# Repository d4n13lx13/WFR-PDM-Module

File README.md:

# WFR-PDM-Module
WFR GLV 2021 PDM PCB
8 fuseholders with diagnosis LEDs, Undervoltage Protection Circuit.

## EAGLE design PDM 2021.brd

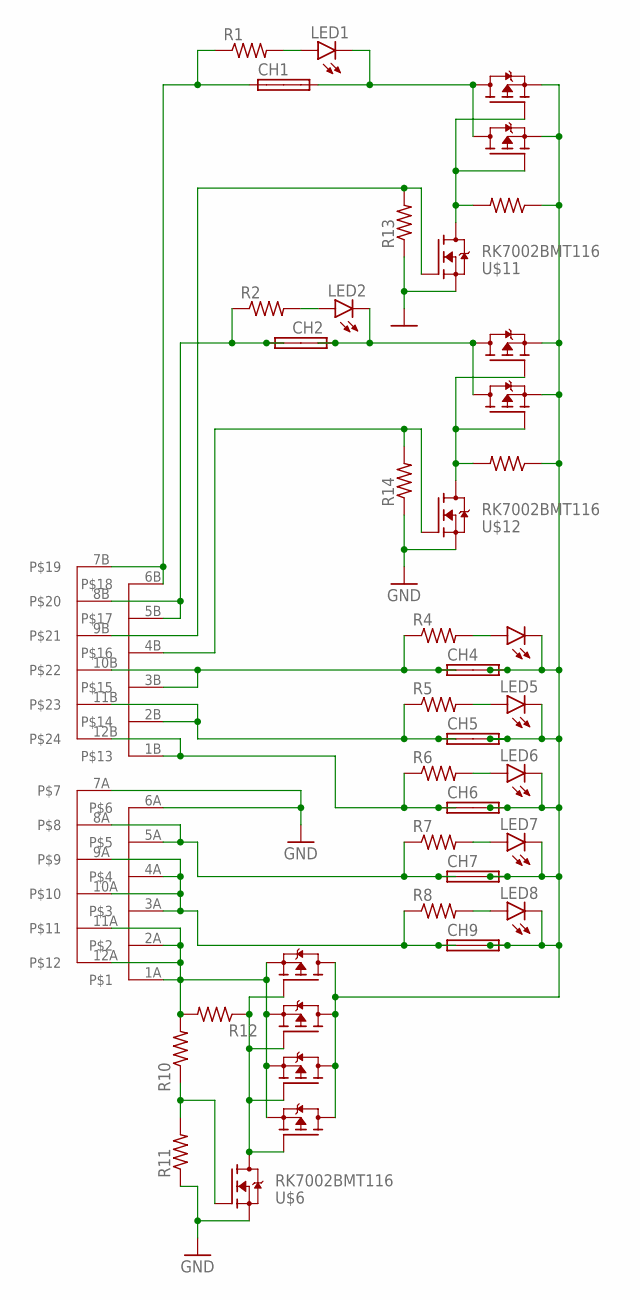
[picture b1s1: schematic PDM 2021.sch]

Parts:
CH1, CH2, CH4, CH5, CH6, CH7, CH9: 3568FUSEHOLDER; 3568
LED1, LED2, LED4, LED5, LED6, LED7, LED8: LEDCHIP-LED0805; CHIP-LED0805
R1, R2, R4, R5, R6, R7, R8, R10, R11, R12, R13, R14, R15, R16: R-US_R0805; R0805
U$1, U$2, U$3, U$5, U$7, U$8, U$9, U$10: _CUSTOM_111_CUSTOM_SQJ407EP-T1_GE3; _CUSTOM_111_CUSTOM_TRANS_SIRA90DP-T1-GE3
U$4: DTM1312PA12BR008; DE_12X2_PIN_HEADER
U$6, U$11, U$12: RK7002BMT116; SOT23

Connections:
CH2: CH2.L1 (1A), CH2.L2 (1B), R2.1, U$4.5B, U$4.8B
CH4: CH4.L1 (1A), CH4.L2 (1B), R4.1, U$4.3B, U$4.10B
CH5: CH5.L1 (1A), CH5.L2 (1B), R5.1, U$4.2B, U$4.11B
CH6: CH6.L1 (1A), CH6.L2 (1B), R6.1, U$4.1B, U$4.12B
CH8: CH7.L1 (1A), CH7.L2 (1B), R7.1, U$4.5A, U$4.8A
CH10: CH9.L1 (1A), CH9.L2 (1B), R8.1, U$4.3A, U$4.4A, U$4.9A, U$4.10A
CH11: CH2.R1 (2A), CH2.R2 (2B), LED2.C, U$9.5 (D), U$10.5 (D)
GND: R11.1, R13.1, R14.1, U$4.6A, U$4.7A, U$6.2 (S), U$11.2 (S), U$12.2 (S)
unnamed: CH4.R1 (2A), CH4.R2 (2B), CH5.R1 (2A), CH5.R2 (2B), CH6.R1 (2A), CH6.R2 (2B), CH7.R1 (2A), CH7.R2 (2B), CH9.R1 (2A), CH9.R2 (2B), LED4.C, LED5.C, LED6.C, LED7.C, LED8.C, R15.1, R16.1, U$1.5 (D), U$2.5 (D), U$3.5 (D), U$5.5 (D), U$7.1 (S), U$7.2 (S), U$7.3 (S), U$8.1 (S), U$8.2 (S), U$8.3 (S), U$9.1 (S), U$9.2 (S), U$9.3 (S), U$10.1 (S), U$10.2 (S), U$10.3 (S)
unnamed: LED8.A, R8.2
unnamed: LED7.A, R7.2
unnamed: LED6.A, R6.2
unnamed: LED5.A, R5.2
unnamed: LED4.A, R4.2
unnamed: CH1.L1 (1A), R1.1, U$4.6B, U$4.7B
unnamed: LED2.A, R2.2
unnamed: CH1.R1 (2A), LED1.C, U$7.5 (D), U$8.5 (D)
unnamed: R10.1, R11.2, U$6.1 (G)
unnamed: R12.1, U$1.4 (G), U$2.4 (G), U$3.4 (G), U$5.4 (G), U$6.3 (D)
unnamed: R16.2, U$7.4 (G), U$8.4 (G), U$11.3 (D)
unnamed: R13.2, U$4.9B, U$11.1 (G)
unnamed: R10.2, R12.2, U$1.1 (S), U$1.2 (S), U$1.3 (S), U$2.1 (S), U$2.2 (S), U$2.3 (S), U$3.1 (S), U$3.2 (S), U$3.3 (S), U$4.1A, U$4.2A, U$4.11A, U$4.12A, U$5.1 (S), U$5.2 (S), U$5.3 (S)
unnamed: R15.2, U$9.4 (G), U$10.4 (G), U$12.3 (D)
unnamed: LED1.A, R1.2
unnamed: R14.2, U$4.4B, U$12.1 (G)

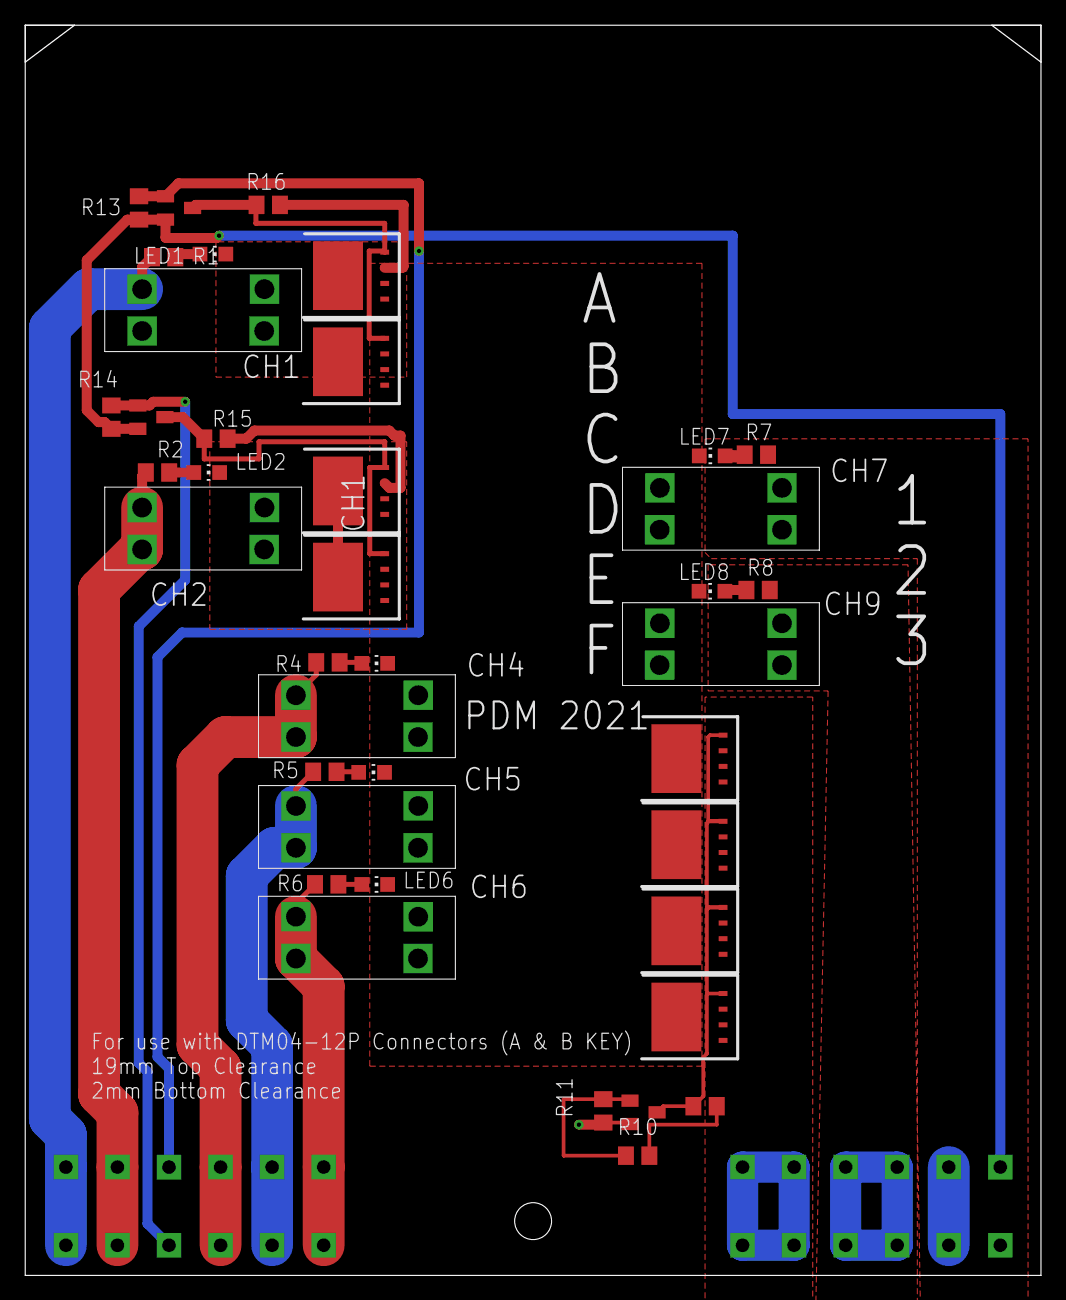
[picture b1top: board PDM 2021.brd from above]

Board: 2 copper layers, 82.5 x 101.6 mm, 40 parts (0 on the bottom side), 25 nets.

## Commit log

2021-10-06 bruh
